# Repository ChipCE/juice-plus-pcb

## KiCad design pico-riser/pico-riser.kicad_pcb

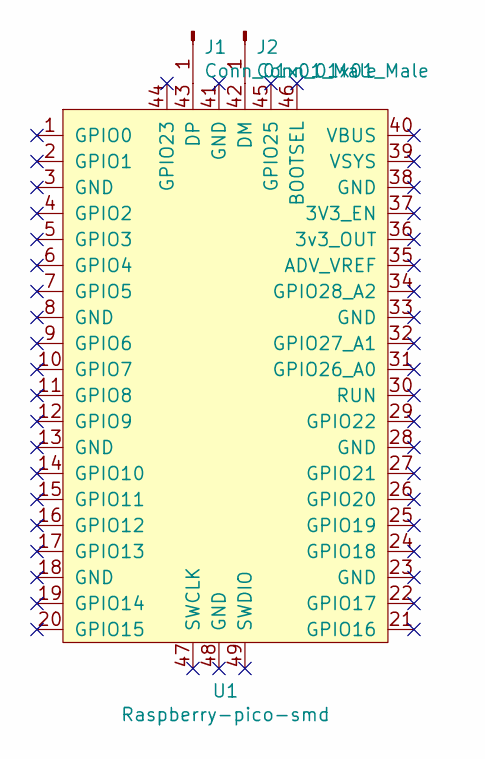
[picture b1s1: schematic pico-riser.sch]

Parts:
J1, J2: Conn_01x01_Male; PinHeader_1x01_P2.54mm_Vertical
U1: Raspberry-pico-smd

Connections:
unnamed: J1.1, U1.43 (DP)
unnamed: J2.1, U1.42 (DM)

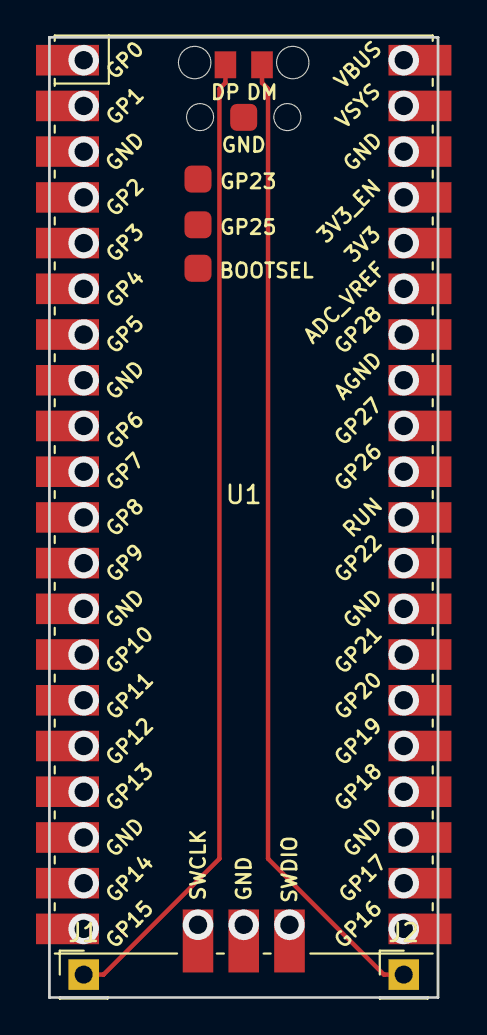
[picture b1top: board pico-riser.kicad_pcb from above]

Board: 2 copper layers, 21.6 x 53.3 mm, 3 parts (0 on the bottom side), 2 nets.

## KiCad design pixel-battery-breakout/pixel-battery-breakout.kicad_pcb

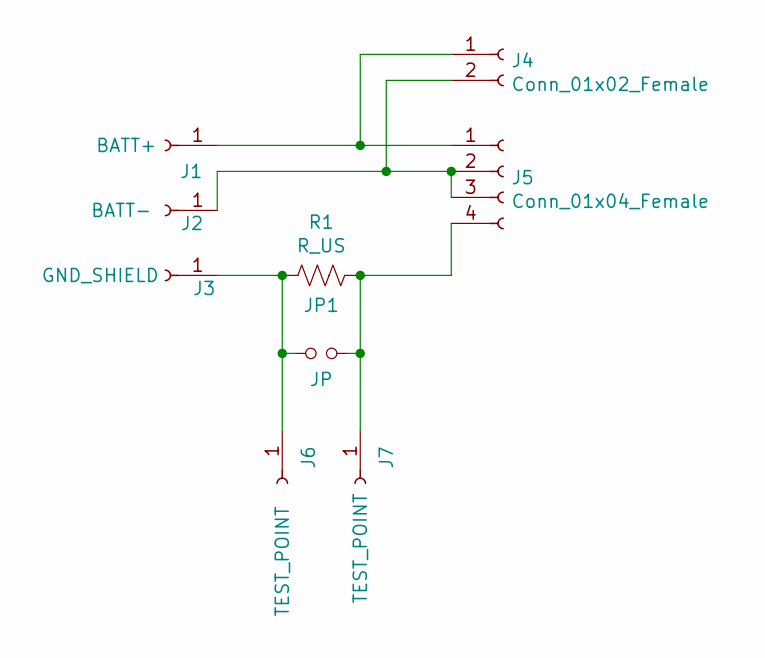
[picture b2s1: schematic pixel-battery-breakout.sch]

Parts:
J1: BATT+; solder-pad
J2: BATT-; solder-pad
J3: GND_SHIELD; solder-pad
J4: Conn_01x02_Female; JST_XH_B2B-XH-A_1x02_P2.50mm_Vertical
J5: Conn_01x04_Female; JST_XH_B4B-XH-A_1x04_P2.50mm_Vertical
J6, J7: TEST_POINT; solder-pad
JP1: JP; SolderJumper-2_P1.3mm_Open_RoundedPad1.0x1.5mm
R1: R_US; R_0805_2012Metric_Pad1.20x1.40mm_HandSolder

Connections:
unnamed: J1.1, J4.1, J5.1
unnamed: J2.1, J4.2, J5.2, J5.3
unnamed: J3.1, J6.1, JP1.1, R1.2
unnamed: J5.4, J7.1, JP1.2, R1.1

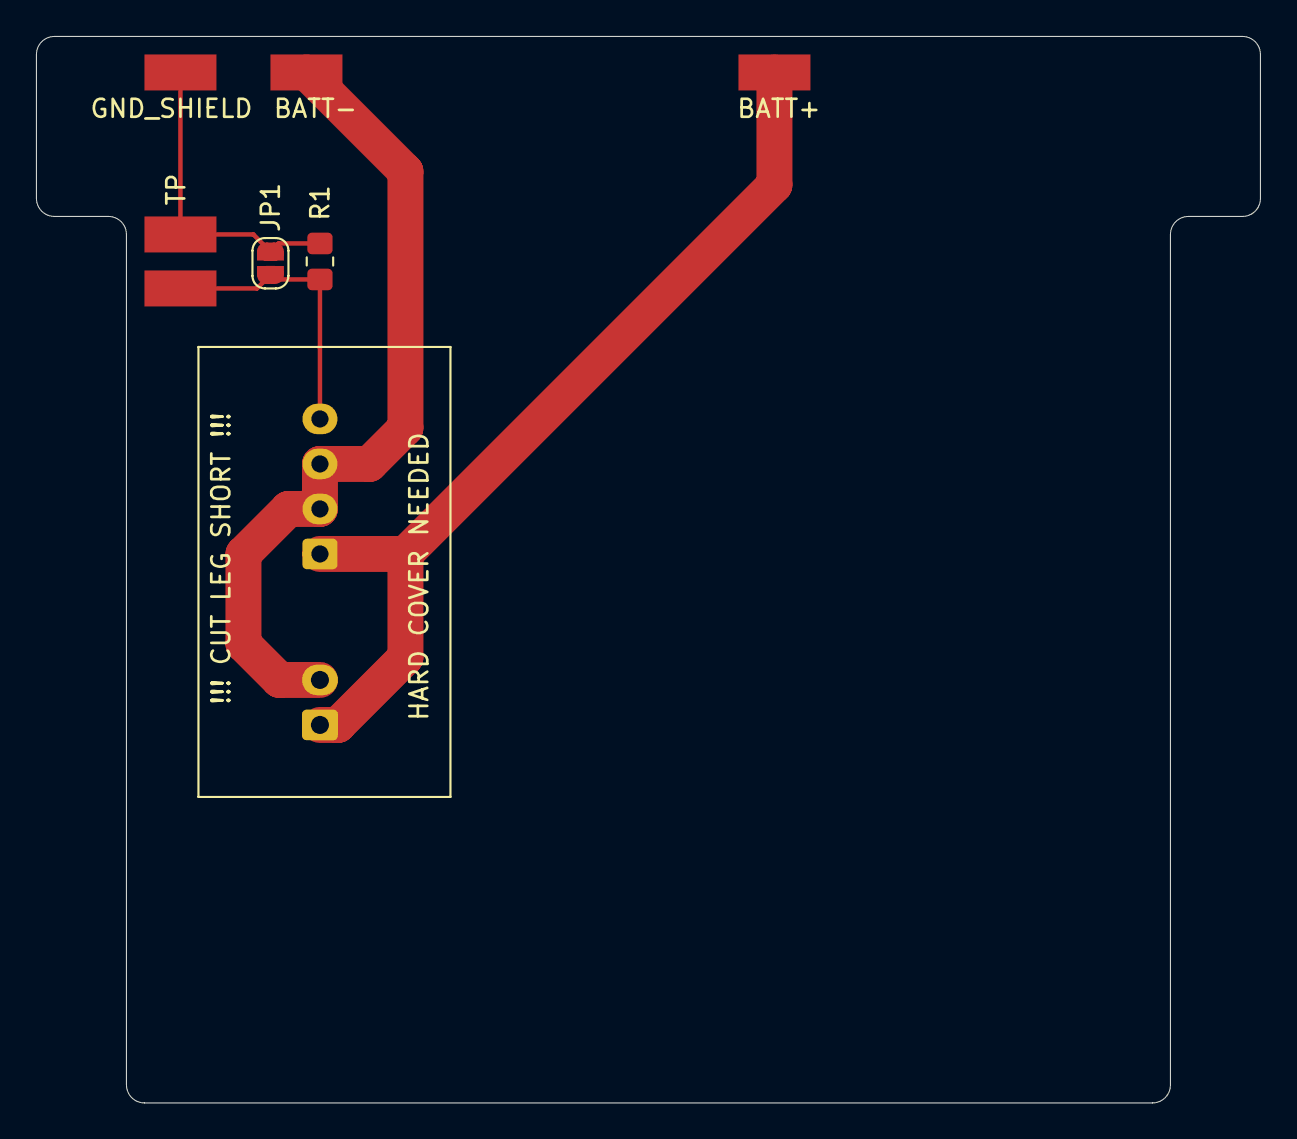
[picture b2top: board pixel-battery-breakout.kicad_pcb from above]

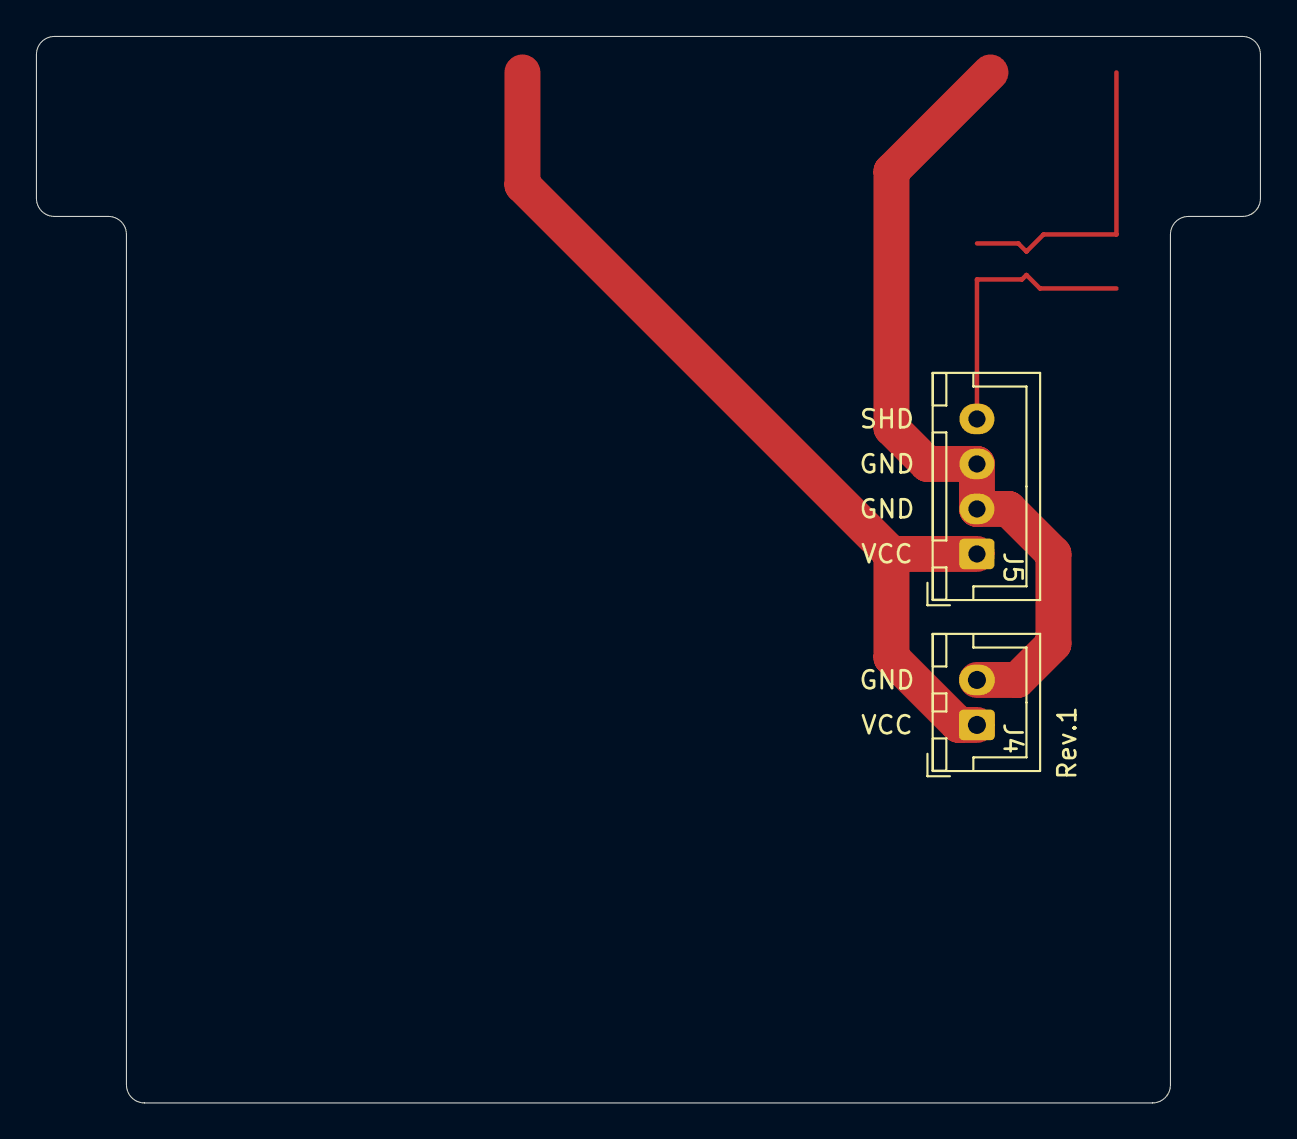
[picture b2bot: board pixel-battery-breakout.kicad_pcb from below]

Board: 2 copper layers, 68.0 x 59.2 mm, 9 parts (2 on the bottom side), 4 nets.

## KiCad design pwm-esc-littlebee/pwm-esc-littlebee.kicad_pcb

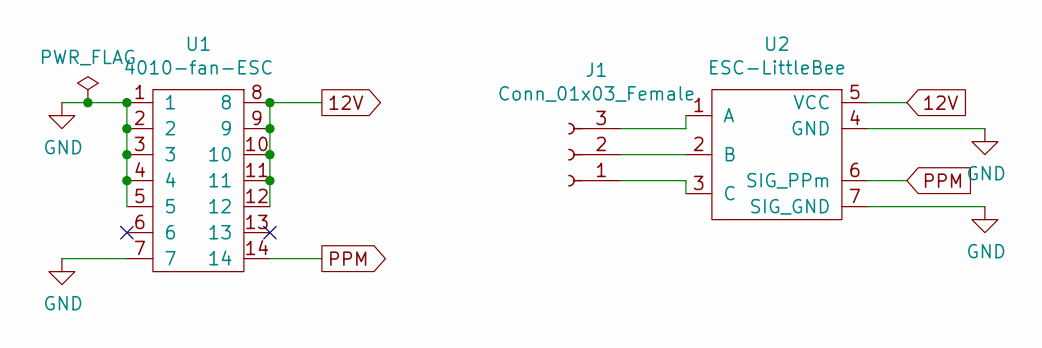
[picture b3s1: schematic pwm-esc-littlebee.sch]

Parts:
J1: Conn_01x03_Female; JST_XH_S03B-XH-A_1x03_P2.50mm_Horizontal
U1: 4010-fan-ESC
U2: ESC-LittleBee; ECS_LittleBee-20A

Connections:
12V: U1.8, U1.9, U1.10, U1.11, U1.12, U2.5 (VCC)
GND: U1.1, U1.2, U1.3, U1.4, U1.5, U1.7, U2.4 (GND), U2.7 (SIG_GND)
unnamed: J1.1, U2.3 (C)
unnamed: J1.2, U2.2 (B)
unnamed: J1.3, U2.1 (A)
PPM: U1.14, U2.6 (SIG_PPm)

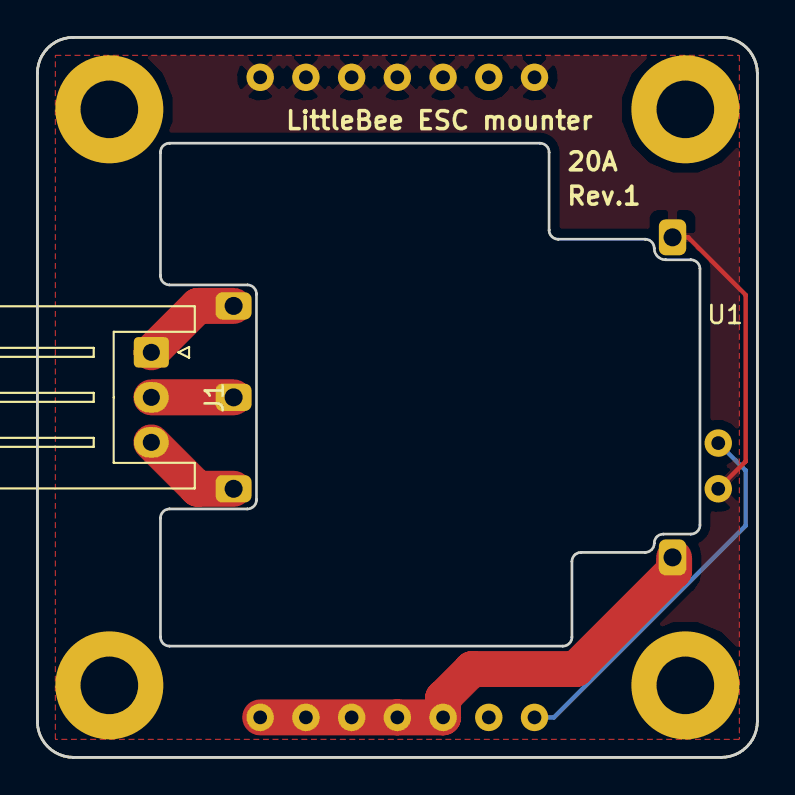
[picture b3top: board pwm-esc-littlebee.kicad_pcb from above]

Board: 2 copper layers, 40.0 x 40.0 mm, 3 parts (1 on the bottom side), 6 nets.

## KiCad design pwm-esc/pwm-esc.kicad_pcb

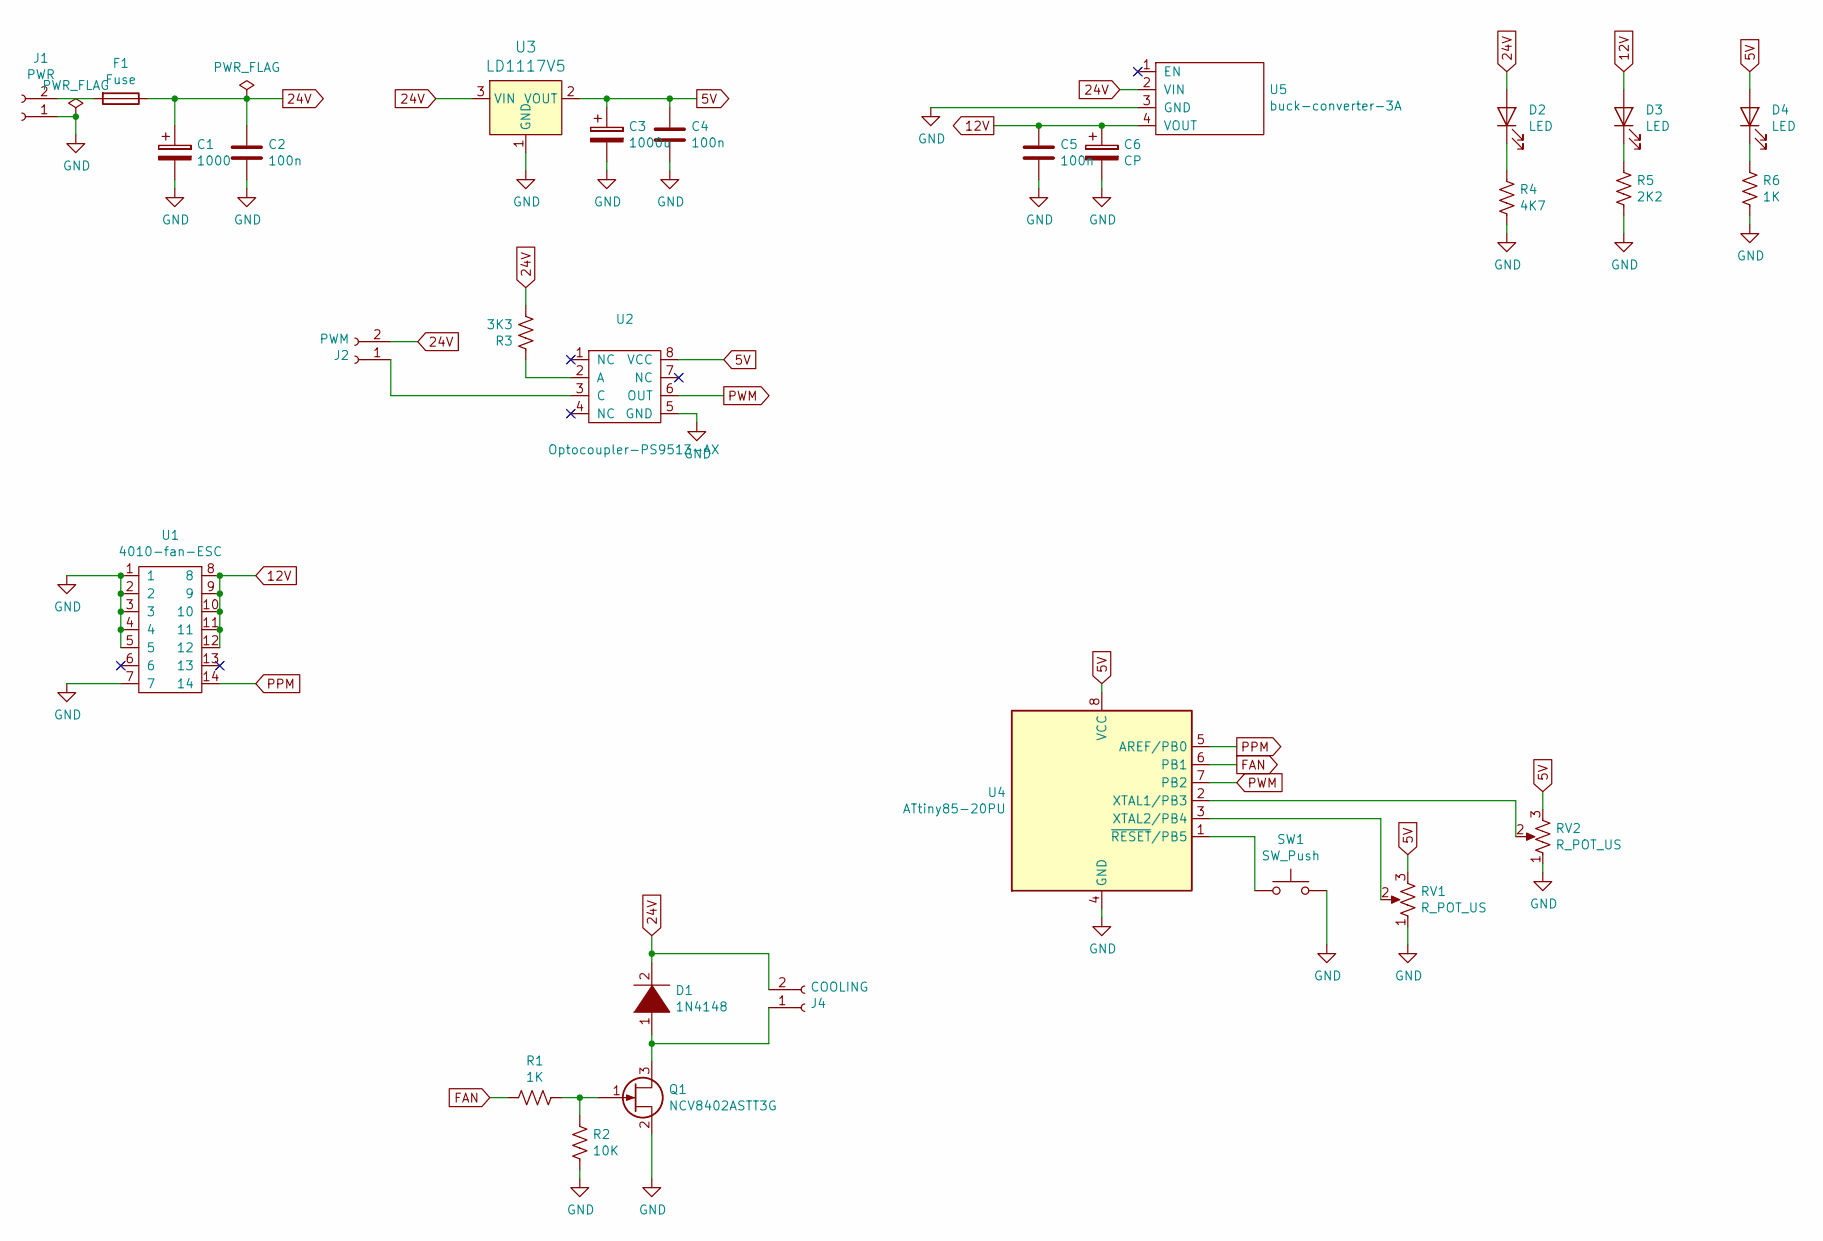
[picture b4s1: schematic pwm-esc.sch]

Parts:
C1: 1000; CP_Radial_D16.0mm_P7.50mm
C2, C4, C5: 100n; C_0805_2012Metric_Pad1.15x1.40mm_HandSolder
C3: 1000u; CP_Radial_D8.0mm_P3.50mm
C6: CP; CP_Radial_D16.0mm_P7.50mm
D1: 1N4148; LED_1206_3216Metric_Pad1.42x1.75mm_HandSolder
D2, D3, D4: LED; LED_0805_2012Metric_Pad1.15x1.40mm_HandSolder
F1: Fuse; Fuse_2920_7451Metric_Pad2.10x5.45mm_HandSolder
J1: PWR; JST_XH_B02B-XH-A_1x02_P2.50mm_Vertical
J2: PWM; JST_XH_B02B-XH-A_1x02_P2.50mm_Vertical
J4: COOLING; JST_XH_B02B-XH-A_1x02_P2.50mm_Vertical
Q1: NCV8402ASTT3G; SOT-223
R1, R6: 1K; R_0805_2012Metric_Pad1.15x1.40mm_HandSolder
R2: 10K; R_0805_2012Metric_Pad1.15x1.40mm_HandSolder
R3: 3K3; R_0805_2012Metric_Pad1.15x1.40mm_HandSolder
R4: 4K7; R_0805_2012Metric_Pad1.15x1.40mm_HandSolder
R5: 2K2; R_0805_2012Metric_Pad1.15x1.40mm_HandSolder
RV1, RV2: R_POT_US; Potentiometer_Vishay_T73YP_Vertical
SW1: SW_Push; SW_PUSH_6mm_H5mm
U1: 4010-fan-ESC
U2: Optocoupler-PS9513-AX; DIP-8_W7.62mm
U3: LD1117V5; SOT-223
U4: ATtiny85-20PU; DIP-8_W7.62mm
U5: buck-converter-3A; Buck-converter-3A

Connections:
5V: C3.1, C4.1, D4.2 (A), RV1.3, RV2.3, U2.8 (VCC), U3.2 (VOUT), U4.8 (VCC)
12V: C5.1, C6.1, D3.2 (A), U1.8, U1.9, U1.10, U1.11, U1.12, U5.4 (VOUT)
24V: C1.1, C2.1, D1.2 (A), D2.2 (A), F1.1, J2.2, J4.2, R3.2, U3.3 (VIN), U5.2 (VIN)
FAN: R1.2, U4.6 (PB1)
GND: C1.2, C2.2, C3.2, C4.2, C5.2, C6.2, J1.1, Q1.2 (S), R2.1, R4.2, R5.2, R6.2, RV1.1, RV2.1, SW1.2, U1.1, U1.2, U1.3, U1.4, U1.5, U1.7, U2.5 (GND), U3.1 (GND), U4.4 (GND), U5.3 (GND)
unnamed: D1.1 (K), J4.1, Q1.3 (D)
unnamed: D2.1 (K), R4.1
unnamed: D3.1 (K), R5.1
unnamed: D4.1 (K), R6.1
unnamed: F1.2, J1.2
unnamed: J2.1, U2.3 (C)
unnamed: Q1.1 (G), R1.1, R2.2
unnamed: R3.1, U2.2 (A)
unnamed: RV1.2, U4.3 (XTAL2/PB4)
unnamed: RV2.2, U4.2 (XTAL1/PB3)
unnamed: SW1.1, U4.1 (~RESET~/PB5)
PPM: U1.14, U4.5 (AREF/PB0)
PWM: U2.6 (OUT), U4.7 (PB2)

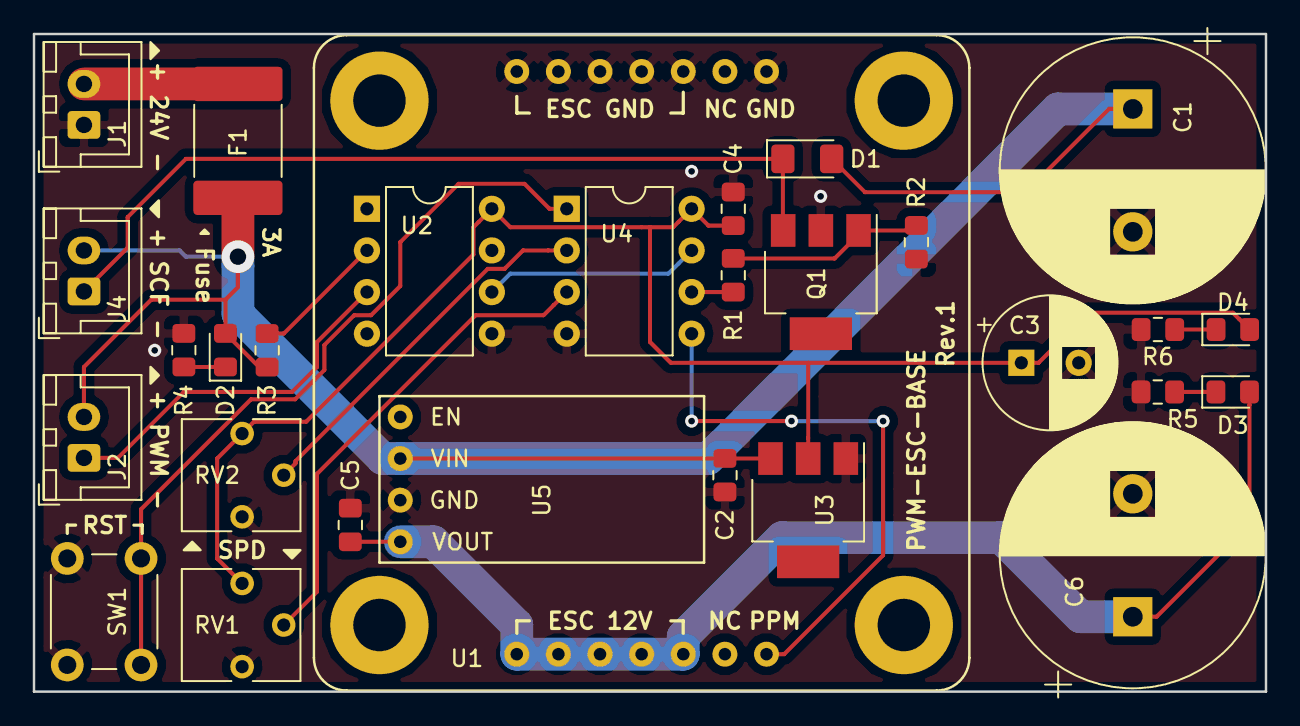
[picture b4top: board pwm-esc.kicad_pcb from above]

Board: 2 copper layers, 75.2 x 40.1 mm, 29 parts (0 on the bottom side), 18 nets.

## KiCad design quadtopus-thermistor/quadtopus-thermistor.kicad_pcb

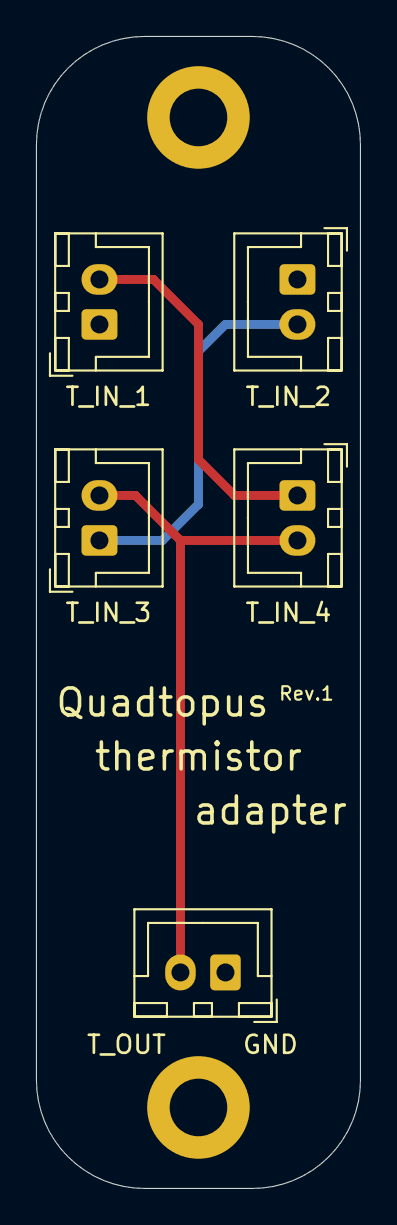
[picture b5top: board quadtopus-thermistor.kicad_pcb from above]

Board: 2 copper layers, 18.0 x 64.0 mm, 5 parts (0 on the bottom side), 4 nets.

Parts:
J1, J2, J3, J4, J5: Conn_01x02_Female; JST_XH_B2B-XH-A_1x02_P2.50mm_Vertical

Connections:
unnamed: J1.1, J3.1, J5.1
unnamed: J1.2, J2.2, J4.2
unnamed: J2.1, J3.2
unnamed: J4.1, J5.2
